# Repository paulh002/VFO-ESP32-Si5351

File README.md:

# VFO-ESP32-Si5351 v3 
v3 is moved to other repository ESPVfo32 the version in this repo is based on older libraries of lvgl 7 and not maintained by me any more.

# VFO-ESP32-Si5351 v2.43 beta
In this version the GUI is changed to support touch using simple buttons at the bottom of the screen.
It took some time to have them also supported by using the rotary encoder.

Changes:
- TFT library has been changed to TFT_eSPI, download the library in Arduine IDE and config the User_Setup.h to your configuration or use the one in this repository for the PCB in this project
- LGVL library is used for GUI. Install in Arduino IDE LVGL library (not Arduino LVGL) copy the lv_conf.h to you library directory to config lvgl library or create your own config file to your liking.
- I use now Visual Studio Community 2019 with Visual Micro to compile the project. But Arduino IDE is also supported.
- source has been moved to vfo_esp32_si5351 directory
- vfo1 and vfo2 support
- gui supported wifi configuration
- gui supported si5351 configuration
- libraries are moved to library directory 
- source code includes a visual studio project file
- TX GUI with power and SWR measurement
- GUI supported AD8307 calibration
- Bfo adjustment, A button select bfo adjustment and use the optical encoder to change frequency.

Notes
- The si5351 library is customized for esp32 support and can be found in the library directory
- Libraries used
   -  Acebutton https://github.com/bxparks/AceButton
   -  ESP32Encoder https://github.com/madhephaestus/ESP32Encoder
   -  lvgl https://lvgl.io/

New GUI with buttons at the bottom   

# VFO-ESP32-Si5351 v2.41 beta
update-- added Power and SWR gauges

# VFO-ESP32-Si5351 v2.4 beta
Version 2.33 source code is moved to the main branch, as I am now working on a new version of the GUI based on LVGL userinterface.
This because the old userinterface became to complex to maintain if I want to add wifi management and other setup pages.
The software is not yet complete, however enough to test.

Gui supported Wifi settings

Gui supported si5351 calibration

# VFO-ESP32-Si5351 v2.33 (main branch)
Updated network functions. Added telnet support for debugging, CAT interface on port 1003 support.
CAT interface will send frequency updates when the VFO is tuned. This is used by RF-AMP and later Antenna tunner to follow the frequencies
See PWRSWR repository for the rf-amp esp32 controler with swr meter functionality. I use same VFO PCB also for rf-amp controler. 

# VFO-ESP32-Si5351 v2.32
Updated the ota software to support Arduino IDE interface, recently I have dropped the Arduino IDE for Visual Studio 2019 which gives a bit more software development support
The main changes for this version is a Network CAT support the idea is from TRXNET (TRX-Manager) unfortunally TRX-Manager is discontinued. But the idea of a CAT interface on tcp/ip is nice. I use this interface to let the VFO to communicate with other ESP32 controlers to automatic send commands to my rf-amp. Also I want to use it to communicate with my automatic antenna tuner. Will be added to github later.

# VFO-ESP32-Si5351 v2.31
Some PCB updates, added output capacitors and changed the resistor pi network on the output to simple voltage divider.
The pi network caused a higher current in the buffer transistor which causes the board to radiate some BFO frequency.
This was picked up by my IF and caused the AGC to react. It seems to be better to lower the current in the buffer transistor.
The output voltage can be regulated by adjusting the resitor divider.

# VFO-ESP32-Si5351 v2.3
I added a new version of the pcb to support Wifi and uses a buck converter for powersupply.
I am still testing if the buck converter does not generate to much noise.
Source code is adjusted to use new GPIO ports so ADC1 is only used

# VFO-ESP32-Si5351 v2.2
Now my transceiver is in a box, it is more easy to update software using wifi. This release support this. The only problem is that some analog ports will not support both ADC and wifi, in the next release I will update the PCB and rearange the analog inputs to user ADC1 only.

# VFO-ESP32-Si5351 v2.1
The PCB has a connector for analog I/O this is intended to support facilities like SWR meter, Voltage and current meter. In the src directory I have put a version of the software that support SWR measurement and CAT interface. Also some simple calibration menu's are added. But this is still in development. The code for SWR comes from Loftur E. Jónasson - TF3LJ / VE2LJX but was intended for Teensy. I made a ESP32 implementation of it and with support for ILI9341 adafruit library. 
I will update (hope fully) this extension the comming months to have full calibration capability for both si5351 and the AD8307 log detectors. A pcb for the SWR meter is also developed this I will put in a seperate repository.

# VFO-ESP32-Si5351 v2.0
The new version v 2.0 uses 2x si5351 on the pcb with buffer transistors to minimize crosstalk. The old version had about 52 db  crosstalk suppression with the new version this is much improved. I cannot hear any injected spurs any more. But will add some measurements later.
The SI5351 library is updated to support multiple si5351's.

If you are using diode double balanced mixers than a square wave is no problem. But if you want to use a jfet balanced mixer than you need to filter the output of the vfo. For this I developed a filter PCB which is controled by the vfo.

Spectrum of two seperate si5351 with buffer. (12.5 Mhz and 8.998 Mhz)

VFO build in into QRP tranceiver with hycas IF and bandpassfilters managed by esp32
The VFO uses a optical encoder for frequency adjustment and mechanical rotary for bandswitch and option selection.

Bottom side with transmitter amplifier and low-pass filter section also managed by esp32.

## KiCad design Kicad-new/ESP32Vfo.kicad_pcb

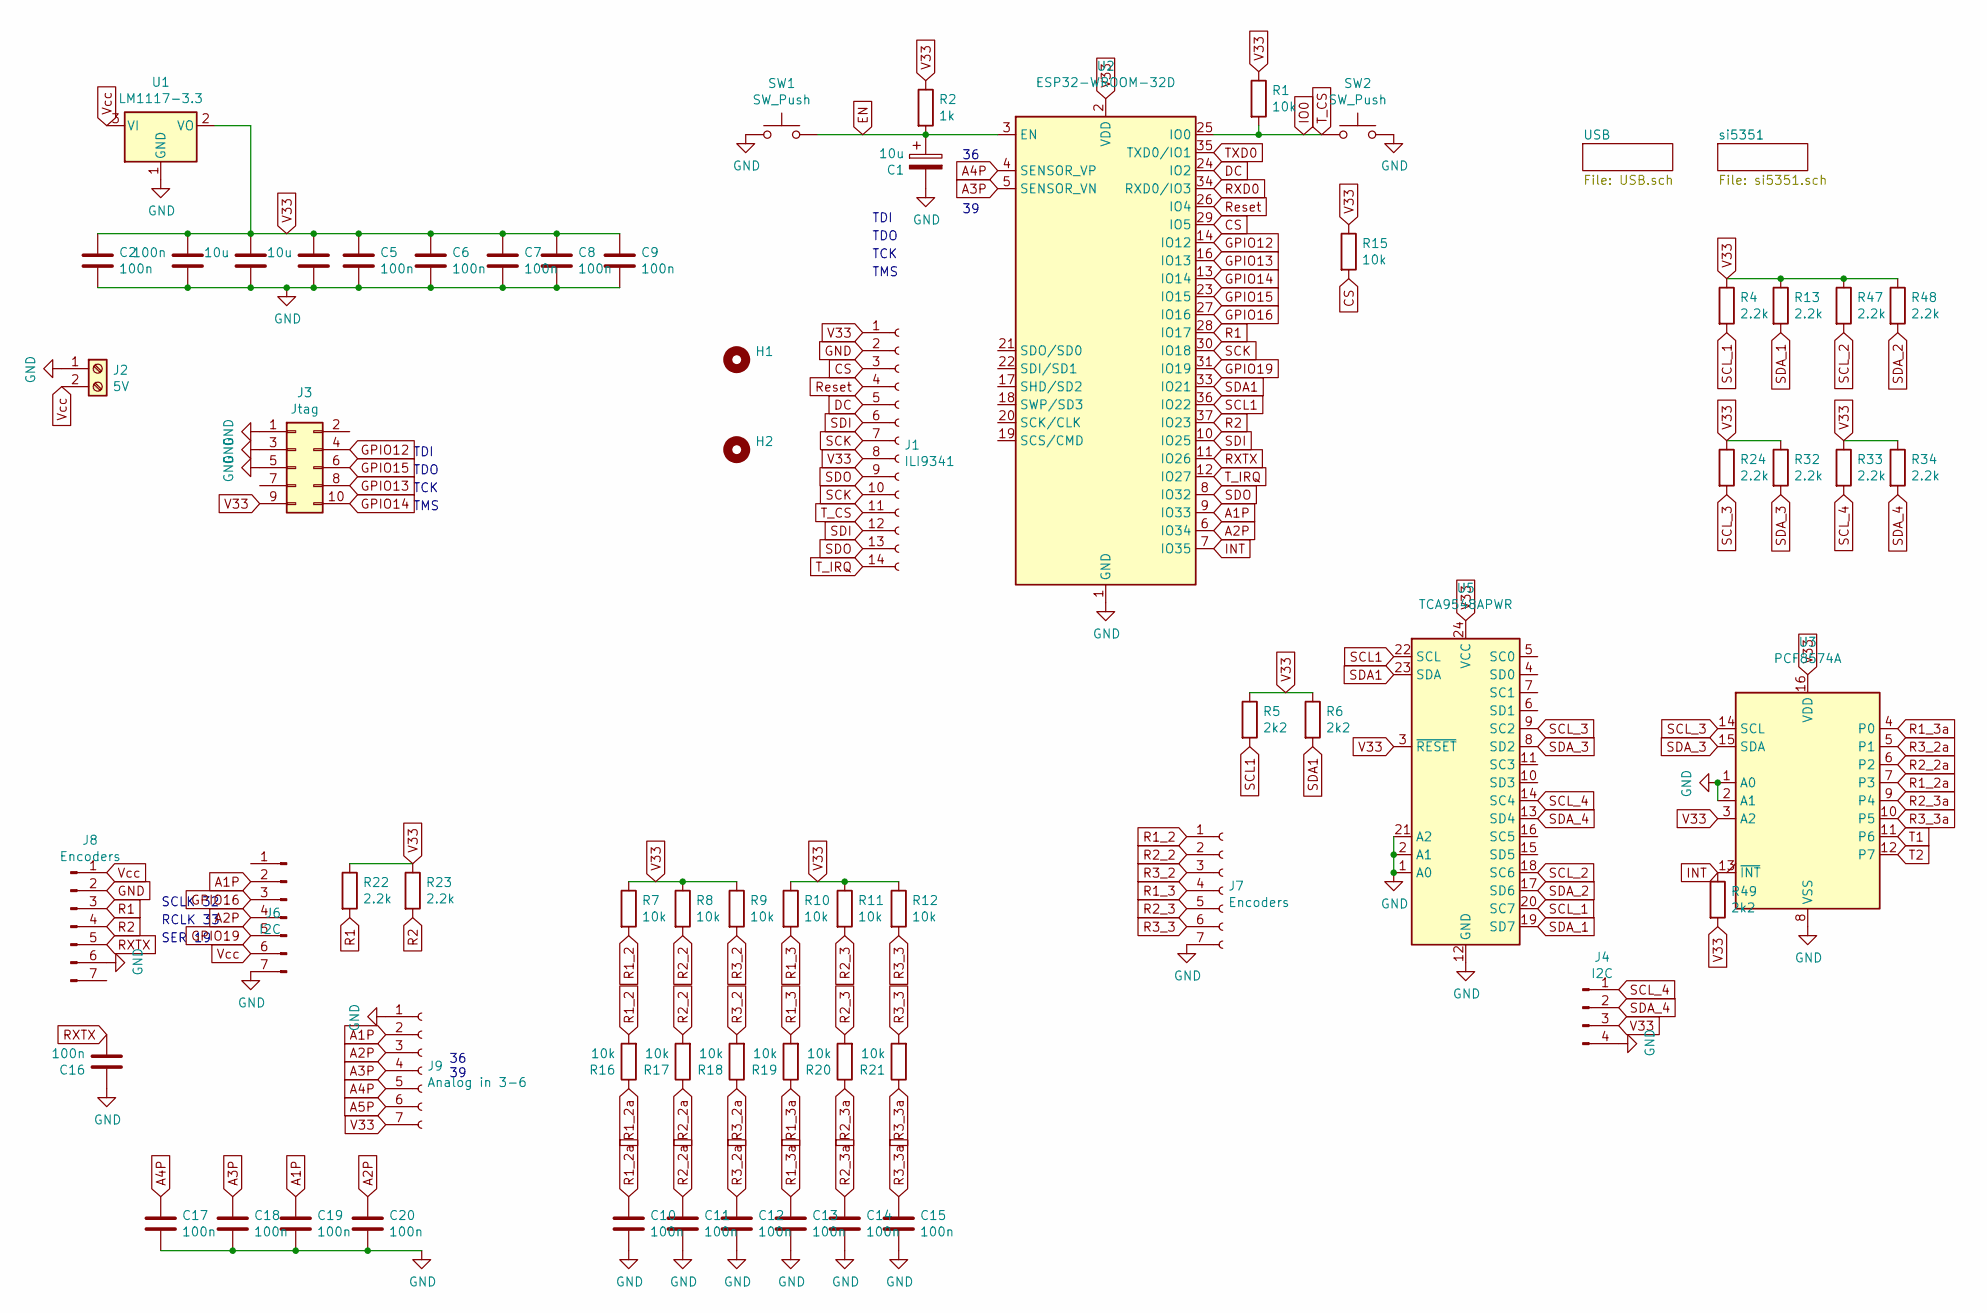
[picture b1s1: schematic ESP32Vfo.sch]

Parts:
C1, C4: 10u; C_1206_3216Metric_Pad1.42x1.75mm_HandSolder
C2, C3, C5, C6, C7, C8, C9, C10, C11, C12, C13, C14, C15, C16, C17, C18, C19, C20: 100n; C_0805_2012Metric
C34: 10u; C_0805_2012Metric
H1, H2: MountingHole_3.2mm_M3
J1: ILI9341; PinSocket_1x14_P2.54mm_Vertical
J2: 5V; TerminalBlock_MetzConnect_Type011_RT05502HBWC_1x02_P5.00mm_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
J3: Jtag; PinSocket_2x05_P2.54mm_Vertical
J4: I2C; JST_PH_S4B-PH-SM4-TB_1x04-1MP_P2.00mm_Horizontal
J6: I2C; PinSocket_1x07_P2.54mm_Vertical
J7, J8: Encoders; PinSocket_1x07_P2.54mm_Vertical
J9: Analog in 3-6; PinSocket_1x07_P2.54mm_Vertical
R1, R7, R8, R9, R10, R11, R12, R15, R16, R17, R18, R19, R20, R21: 10k; R_0805_2012Metric
R2: 1k; R_0805_2012Metric
R4, R13, R22, R23, R24, R32, R33, R34, R47, R48: 2.2k; R_0805_2012Metric
R5, R6, R49: 2k2; R_0805_2012Metric
SW1, SW2: SW_Push; TS-1088R-02526
U1: LM1117-3.3; SOT-223-3_TabPin2
U2: ESP32-WROOM-32D; ESP32-WROOM-32
U3: PCF8574A; SOP-16_7.5x10.4mm_P1.27mm
U5: TCA9548APWR; TSSOP-24_4.4x7.8mm_P0.65mm

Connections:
A1P: C19.2, J6.2, J9.2, U2.9 (IO33)
A2P: C20.2, J6.4, J9.3, U2.6 (IO34)
A3P: C18.2, J9.4, U2.5 (SENSOR_VN)
A4P: C17.2, J9.5, U2.4 (SENSOR_VP)
A5P: J9.6
CS: J1.3, R15.2, U2.29 (IO5)
DC: J1.5, U2.24 (IO2)
EN: C1.1, R2.2, SW1.2, U2.3 (EN); also elsewhere on the board
GND: C1.2, C2.1, C3.2, C4.2, C5.1, C6.1, C7.1, C8.1, C9.1, C10.1, C11.1, C12.1, C13.1, C14.1, C15.1, C16.2, C17.1, C18.1, C19.1, C20.1, C34.2, J1.2, J2.1, J3.1, J3.3, J3.5, J4.4, J6.7, J7.7, J8.2, J8.6, J9.1, SW1.1, SW2.2, U1.1 (GND), U2.1 (GND), U2.15 (GND), U2.38 (GND), U2.39 (GND), U3.1 (A0), U3.2 (A1), U3.8 (VSS), U5.1 (A0), U5.2 (A1), U5.12 (GND), U5.21 (A2); also elsewhere on the board
GPIO12: J3.4, U2.14 (IO12)
GPIO13: J3.8, U2.16 (IO13)
GPIO14: J3.10, U2.13 (IO14)
GPIO15: J3.6, U2.23 (IO15)
GPIO16: J6.3, U2.27 (IO16)
GPIO19: J6.5, U2.31 (IO19)
INT: R49.1, U2.7 (IO35), U3.13 (~INT~)
IO0: J1.11, R1.2, SW2.1, U2.25 (IO0); also elsewhere on the board
R1: J8.3, R22.2, U2.28 (IO17)
R1_2: J7.1, R7.2, R16.2
R1_2a: C10.2, R16.1, U3.7 (P3)
R1_3: J7.4, R10.2, R19.2
R1_3a: C13.2, R19.1, U3.4 (P0)
R2: J8.4, R23.2, U2.37 (IO23)
R2_3: J7.5, R11.2, R20.2
R2_3a: C14.2, R20.1, U3.9 (P4)
R3_2: J7.3, R9.2, R18.2
R3_2a: C12.2, R18.1, U3.5 (P1)
R3_3: J7.6, R12.2, R21.2
R3_3a: C15.2, R21.1, U3.10 (P5)
RXD0: U2.34 (RXD0/IO3); also elsewhere on the board
Reset: J1.4, U2.26 (IO4)
SCK: J1.7, J1.10, U2.30 (IO18)
SCL1: R5.2, U2.36 (IO22), U5.22 (SCL)
SCL_1: R4.2, U5.20 (SC7); also elsewhere on the board
SCL_2: R47.2, U5.18 (SC6); also elsewhere on the board
SCL_3: R24.2, U3.14 (SCL), U5.9 (SC2)
SCL_4: J4.1, R33.2, U5.14 (SC4)
SDA1: R6.2, U2.33 (IO21), U5.23 (SDA)
SDA_1: R13.2, U5.19 (SD7); also elsewhere on the board
SDA_2: R48.2, U5.17 (SD6); also elsewhere on the board
SDA_3: R32.2, U3.15 (SDA), U5.8 (SD2)
SDA_4: J4.2, R34.2, U5.13 (SD4)
SDI: J1.6, J1.12, U2.10 (IO25)
SDO: J1.9, J1.13, U2.8 (IO32)
T1: U3.11 (P6); also elsewhere on the board
T2: U3.12 (P7); also elsewhere on the board
TXD0: U2.35 (TXD0/IO1); also elsewhere on the board
T_IRQ: J1.14, U2.12 (IO27)
Vcc: J2.2, J6.6, J8.1, U1.3 (VI); also elsewhere on the board

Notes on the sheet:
TMS
TCK
TDO
TDI
36 39
SER 19
SCLK 32
RCLK 33

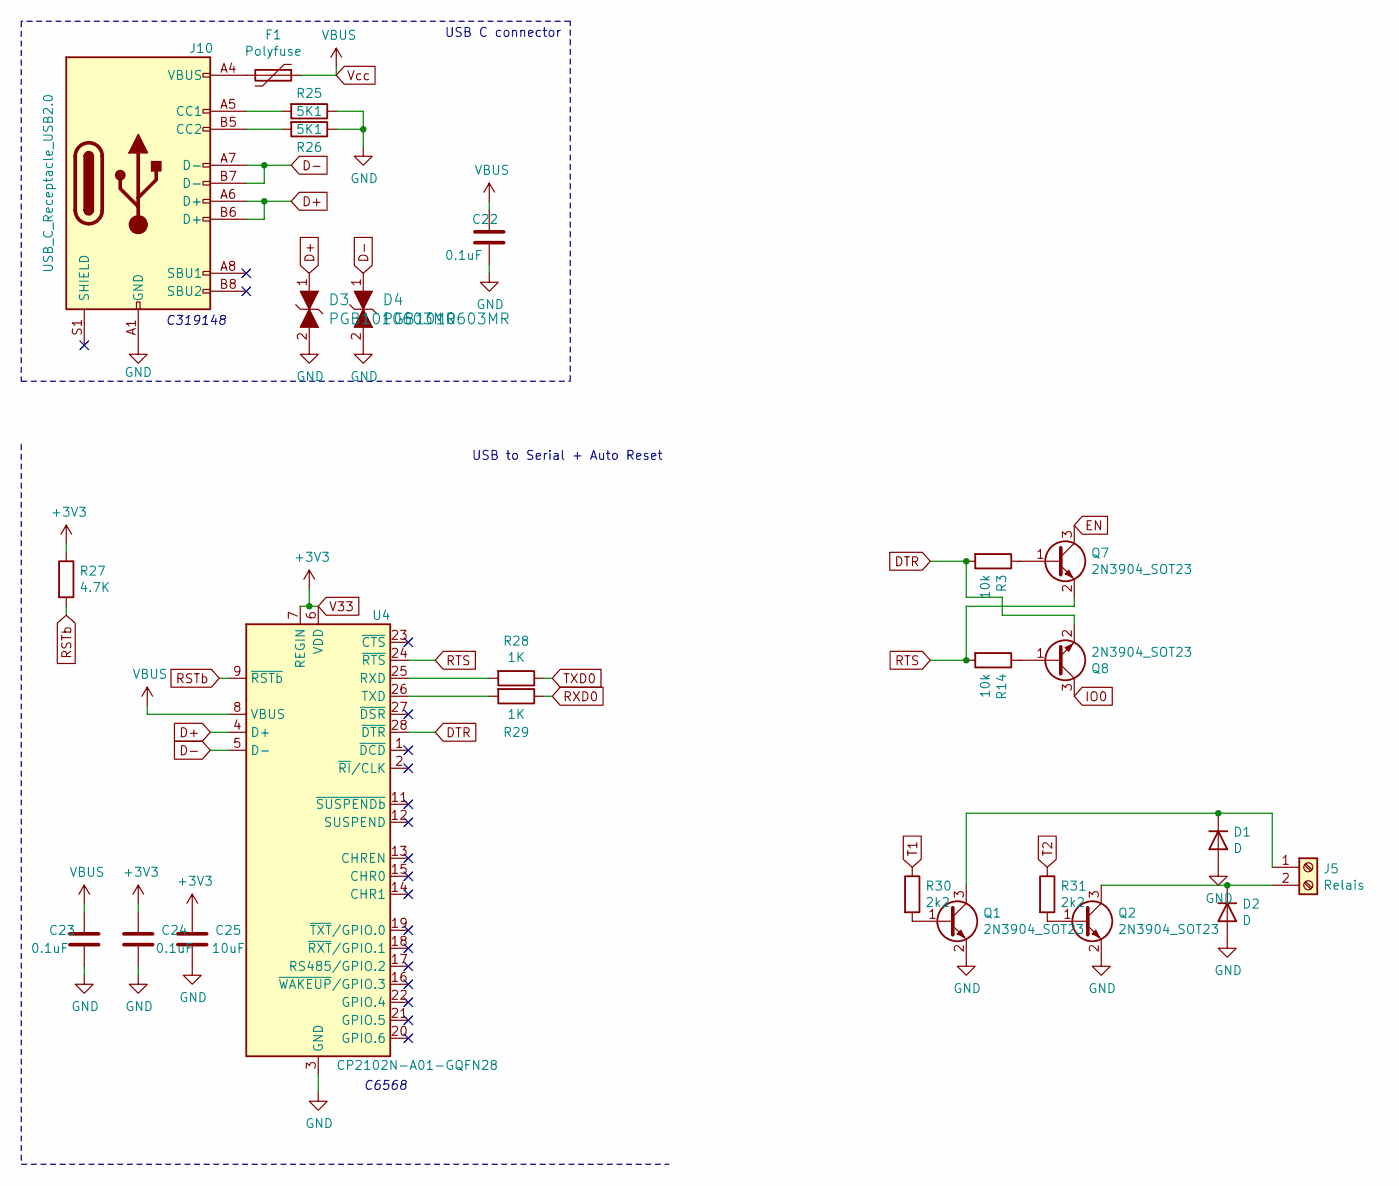
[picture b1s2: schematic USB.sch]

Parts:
C22, C23, C24: 0.1uF; C_0805_2012Metric
C25: 10uF; C_0805_2012Metric
D1, D2: D; D_SOD-323
D3, D4: PGB1010603MR; 0603; MPN PGB1010603MR; Digi-Key_PN F2594CT-ND
F1: Polyfuse; Fuse_0805_2012Metric
J5: Relais; PinHeader_1x02_P2.54mm_Vertical
J10: USB_C_Receptacle_USB2.0; USB_C_Receptacle_XKB_U262-16XN-4BVC11
Q1, Q2, Q7, Q8: 2N3904_SOT23; SOT-23
R3, R14: 10k; R_0805_2012Metric
R25, R26: 5K1; R_0805_2012Metric
R27: 4.7K; R_0805_2012Metric
R28, R29: 1K; R_0805_2012Metric
R30, R31: 2k2; R_0805_2012Metric
U4: CP2102N-A01-GQFN28; QFN-28-1EP_5x5mm_P0.5mm_EP3.35x3.35mm

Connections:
D+: D3.1, J10.A6 (D+), J10.B6 (D+), U4.4 (D+)
D-: D4.1, J10.A7 (D-), J10.B7 (D-), U4.5 (D-)
DTR: Q8.2 (E), R3.2, U4.28 (~DTR)
EN: Q7.3 (C); also elsewhere on the board
GND: C22.2, C23.2, C24.2, C25.2, D1.2 (A), D2.2 (A), D3.2, D4.2, J10.A1 (GND), J10.A12 (GND), J10.B1 (GND), J10.B12 (GND), Q1.2 (E), Q2.2 (E), R25.1, R26.1, U4.3 (GND), U4.29 (GND); also elsewhere on the board
IO0: Q8.3 (C); also elsewhere on the board
unnamed: D1.1 (K), J5.1, Q1.3 (C)
unnamed: D2.1 (K), J5.2, Q2.3 (C)
unnamed: F1.2, J10.A4 (VBUS), J10.A9 (VBUS), J10.B4 (VBUS), J10.B9 (VBUS)
unnamed: J10.A5 (CC1), R25.2
unnamed: J10.B5 (CC2), R26.2
unnamed: Q1.1 (B), R30.2
unnamed: Q2.1 (B), R31.2
unnamed: Q7.1 (B), R3.1
unnamed: Q8.1 (B), R14.1
unnamed: R28.2, U4.25 (RXD)
unnamed: R29.2, U4.26 (TXD)
RSTb: R27.2, U4.9 (~RSTb)
RTS: Q7.2 (E), R14.2, U4.24 (~RTS)
RXD0: R29.1; also elsewhere on the board
T1: R30.1; also elsewhere on the board
T2: R31.1; also elsewhere on the board
TXD0: R28.1; also elsewhere on the board
Vcc: C22.1, C23.1, F1.1, U4.8 (VBUS); also elsewhere on the board

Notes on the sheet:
C6568
USB to Serial + Auto Reset
USB C connector
C319148

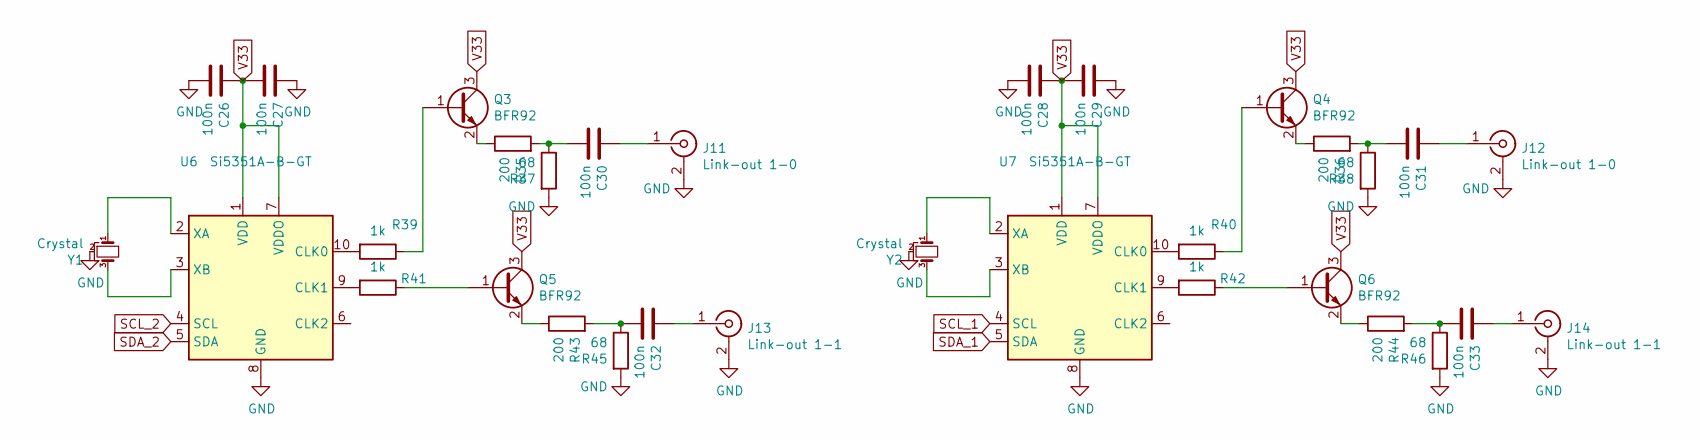
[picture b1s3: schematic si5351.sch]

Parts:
C26, C27, C28, C29, C30, C31, C32, C33: 100n; C_0805_2012Metric
J11, J12: Link-out 1-0; SMA_Amphenol_132134_Vertical
J13, J14: Link-out 1-1; SMA_Amphenol_132134_Vertical
Q3, Q4, Q5, Q6: BFR92; SOT-23
R35, R36, R43, R44: 200; R_0805_2012Metric
R37, R38, R45, R46: 68; R_0805_2012Metric
R39, R40, R41, R42: 1k; R_0805_2012Metric
U6, U7: Si5351A-B-GT; MSOP-10_3x3mm_P0.5mm
Y1, Y2: Crystal; Crystal_SMD_TXC_7M-4Pin_3.2x2.5mm_HandSoldering

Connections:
GND: C26.1, C27.2, C28.1, C29.2, J11.2 (Ext), J12.2 (Ext), J13.2 (Ext), J14.2 (Ext), R37.2, R38.2, R45.2, R46.2, U6.8 (GND), U7.8 (GND), Y1.2, Y2.2; also elsewhere on the board
unnamed: C30.1, R35.2, R37.1
unnamed: C30.2, J11.1 (In)
unnamed: C31.1, R36.2, R38.1
unnamed: C31.2, J12.1 (In)
unnamed: C32.1, R43.2, R45.1
unnamed: C32.2, J13.1 (In)
unnamed: C33.1, R44.2, R46.1
unnamed: C33.2, J14.1 (In)
unnamed: Q3.1 (B), R39.1
unnamed: Q3.2 (E), R35.1
unnamed: Q4.1 (B), R40.1
unnamed: Q4.2 (E), R36.1
unnamed: Q5.1 (B), R41.1
unnamed: Q5.2 (E), R43.1
unnamed: Q6.1 (B), R42.1
unnamed: Q6.2 (E), R44.1
unnamed: R39.2, U6.10 (CLK0)
unnamed: R40.2, U7.10 (CLK0)
unnamed: R41.2, U6.9 (CLK1)
unnamed: R42.2, U7.9 (CLK1)
unnamed: U6.2 (XA), Y1.1
unnamed: U6.3 (XB), Y1.3
unnamed: U7.2 (XA), Y2.1
unnamed: U7.3 (XB), Y2.3
SCL_1: U7.4 (SCL); also elsewhere on the board
SCL_2: U6.4 (SCL); also elsewhere on the board
SDA_1: U7.5 (SDA); also elsewhere on the board
SDA_2: U6.5 (SDA); also elsewhere on the board

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
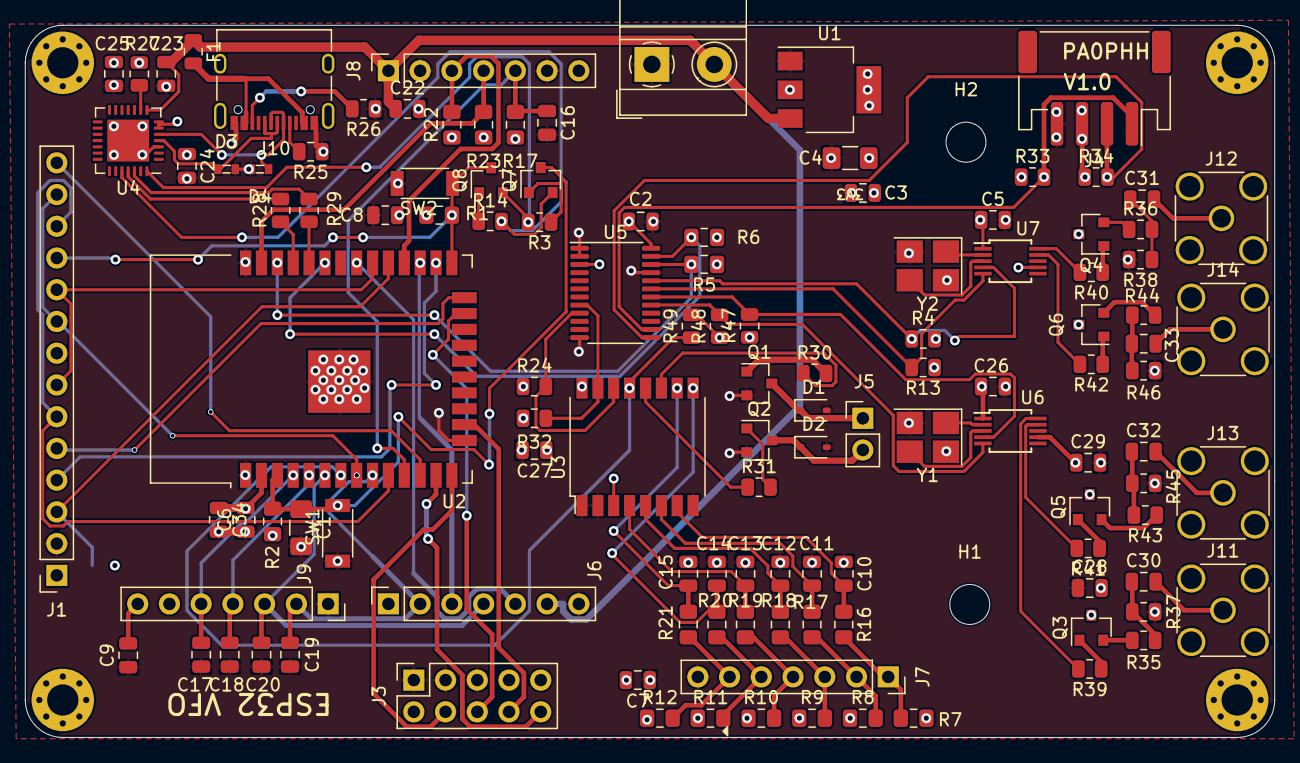
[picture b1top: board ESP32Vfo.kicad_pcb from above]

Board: 4 copper layers, 100.0 x 57.0 mm, 127 parts (1 on the bottom side), 92 nets.

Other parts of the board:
H1#2, H2#2, H3, H4: MountingHole; MountingHole_2.5mm_Pad_Via
R17#2: 10k; R_0805_2012Metric_Pad1.15x1.40mm_HandSolder

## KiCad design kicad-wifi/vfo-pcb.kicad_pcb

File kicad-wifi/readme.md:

Kicad files new version with wifi.
This version uses a buck converter for powersupply, the lm7805 is not able to supply a stable enough 5v for wifi use
I am still testing if the buck converter does not generate to much noise

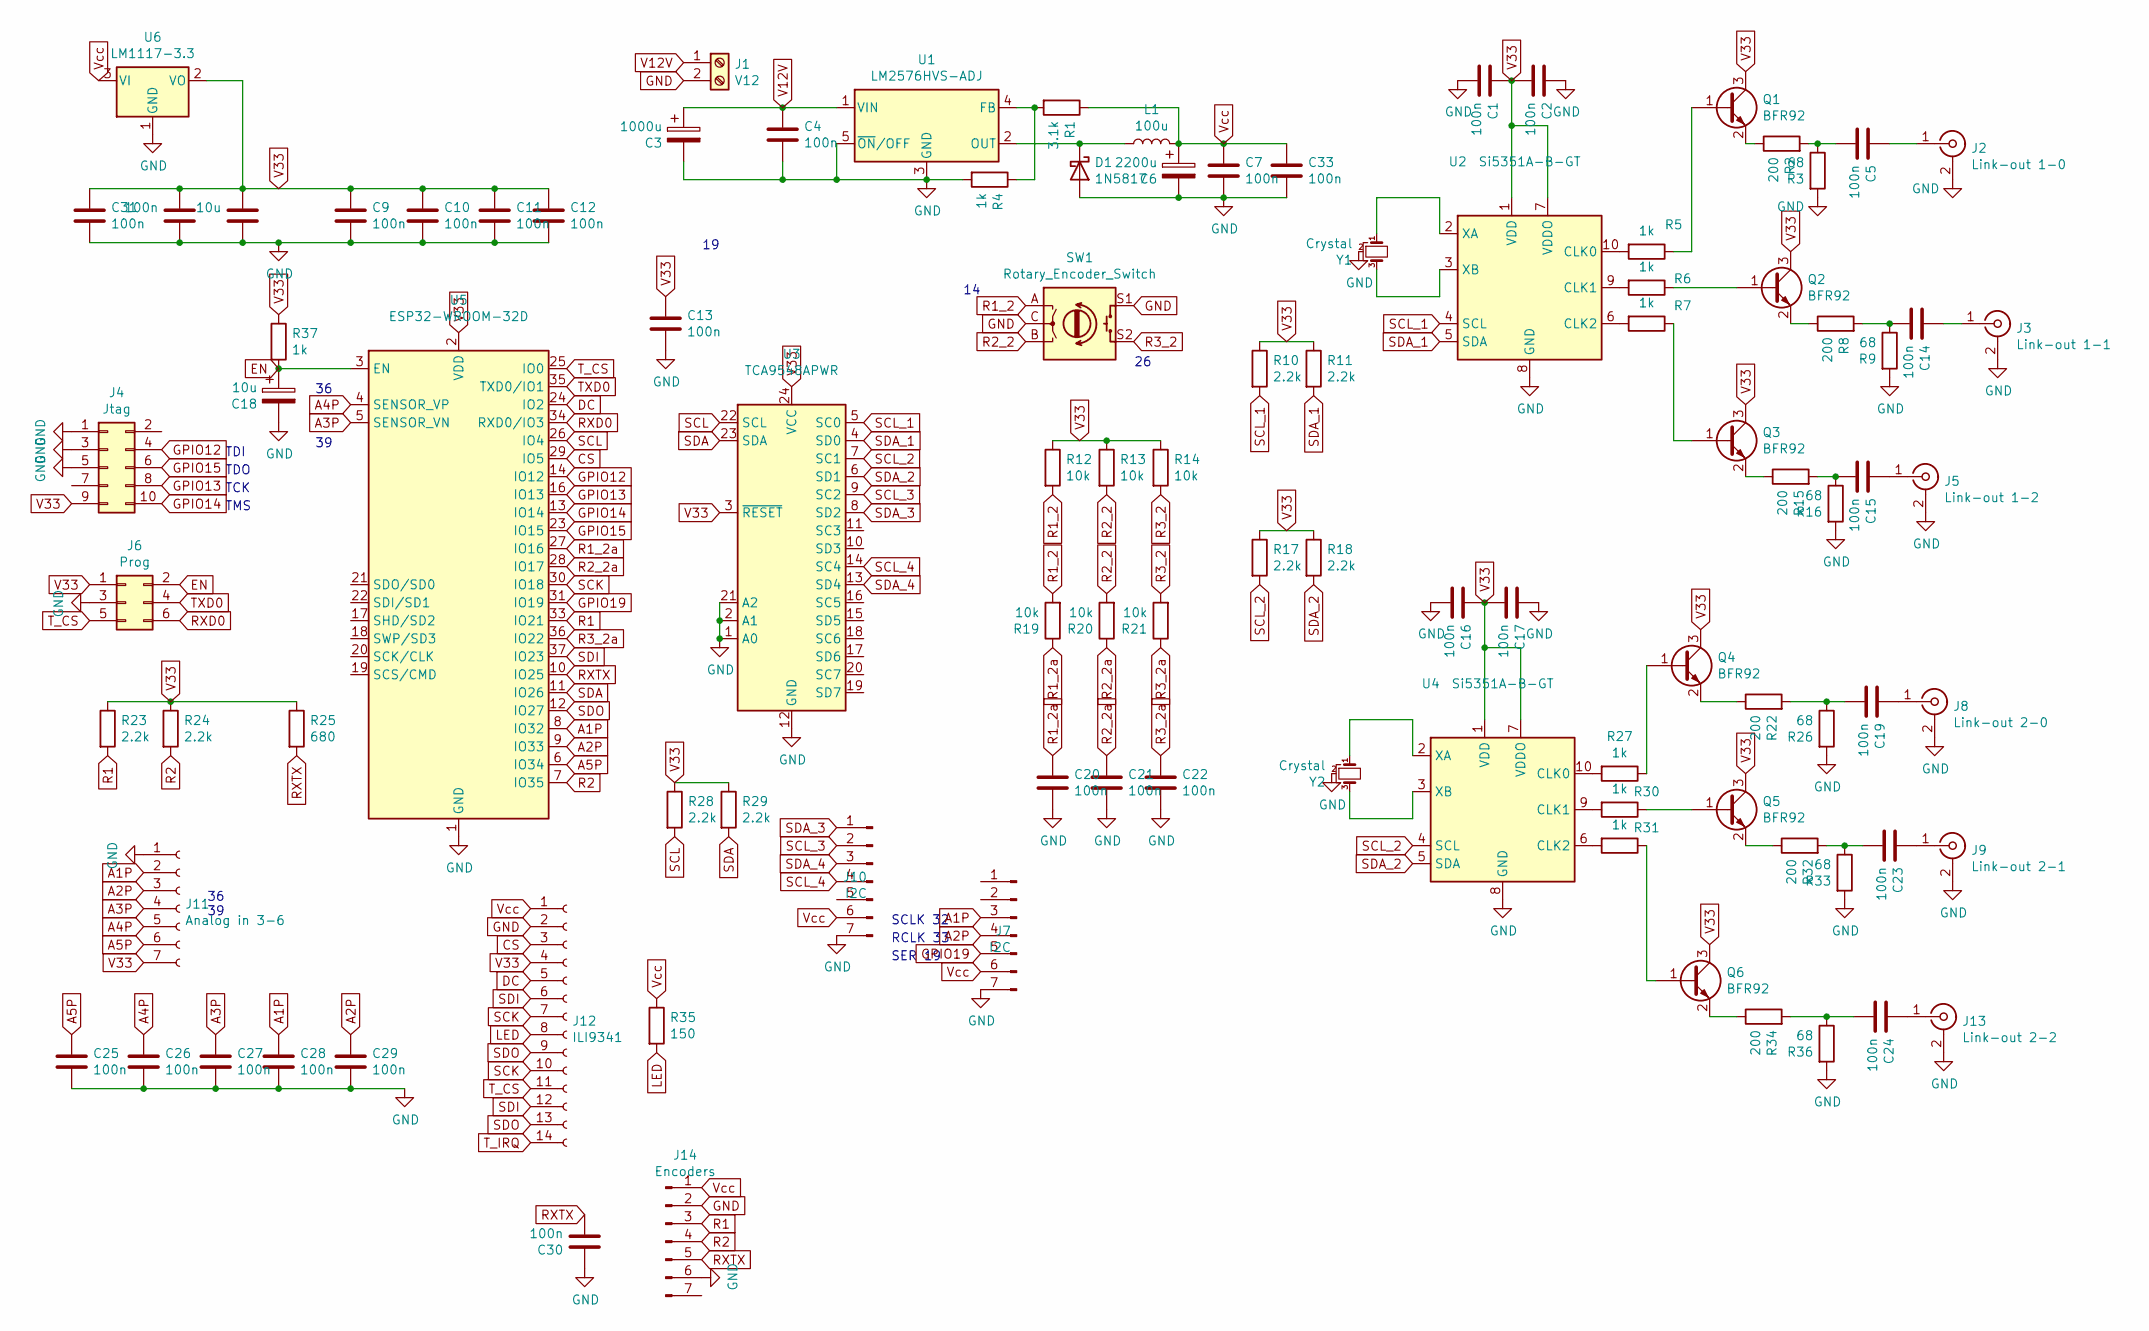
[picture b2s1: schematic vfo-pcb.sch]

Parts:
C1, C2, C4, C5, C7, C8, C9, C10, C11, C12, C13, C14, C15, C16, C17, C19, C20, C21, C22, C23, C24, C25, C26, C27, C28, C29, C30, C31, C33: 100n; C_1206_3216Metric_Pad1.42x1.75mm_HandSolder
C3: 1000u; CP_Radial_D10.0mm_P5.00mm
C6: 2200u; CP_Radial_D10.0mm_P5.00mm
C18, C32: 10u; C_1206_3216Metric_Pad1.42x1.75mm_HandSolder
D1: 1N5817; D_DO-41_SOD81_P10.16mm_Horizontal
J1: V12; TerminalBlock_MetzConnect_Type011_RT05502HBWC_1x02_P5.00mm_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
J2: Link-out 1-0; SMA_Amphenol_132134_Vertical
J3: Link-out 1-1; SMA_Amphenol_132134_Vertical
J4: Jtag; PinSocket_2x05_P2.54mm_Vertical
J5: Link-out 1-2; SMA_Amphenol_132134_Vertical
J6: Prog; PinSocket_2x03_P2.54mm_Vertical
J7, J10: I2C; PinSocket_1x07_P2.54mm_Vertical
J8: Link-out 2-0; SMA_Amphenol_132134_Vertical
J9: Link-out 2-1; SMA_Amphenol_132134_Vertical
J11: Analog in 3-6; PinSocket_1x07_P2.54mm_Vertical
J12: ILI9341; PinSocket_1x14_P2.54mm_Vertical
J13: Link-out 2-2; SMA_Amphenol_132134_Vertical
J14: Encoders; PinSocket_1x07_P2.54mm_Vertical
L1: 100u; L_Bourns-SRU1028_10.0x10.0mm
Q1, Q2, Q3, Q4, Q5, Q6: BFR92; SOT-23
R1: 3.1k; R_1206_3216Metric_Pad1.42x1.75mm_HandSolder
R2, R8, R15, R22, R32, R34: 200; R_1206_3216Metric_Pad1.42x1.75mm_HandSolder
R3, R9, R16, R26, R33, R36: 68; R_1206_3216Metric_Pad1.42x1.75mm_HandSolder
R4, R5, R6, R7, R27, R30, R31, R37: 1k; R_1206_3216Metric_Pad1.42x1.75mm_HandSolder
R10, R11, R17, R18, R23, R24, R28, R29: 2.2k; R_1206_3216Metric_Pad1.42x1.75mm_HandSolder
R12, R13, R14, R19, R20, R21: 10k; R_1206_3216Metric_Pad1.42x1.75mm_HandSolder
R25: 680; R_1206_3216Metric_Pad1.42x1.75mm_HandSolder
R35: 150; R_1206_3216Metric_Pad1.42x1.75mm_HandSolder
SW1: Rotary_Encoder_Switch; RotaryEncoder_Alps_EC11E-Switch_Vertical_H20mm
U1: LM2576HVS-ADJ; TO-220-5_Horizontal_TabDown
U2, U4: Si5351A-B-GT; MSOP-10_3x3mm_P0.5mm
U3: TCA9548APWR; TSSOP-24_4.4x7.8mm_P0.65mm
U5: ESP32-WROOM-32D; ESP32-WROOM-32
U6: LM1117-3.3; SOT-223-3_TabPin2
Y1, Y2: Crystal; Crystal_SMD_TXC_7M-4Pin_3.2x2.5mm_HandSoldering

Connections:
A1P: C28.2, J7.3, J11.2, U5.8 (IO32)
A2P: C29.2, J7.4, J11.3, U5.9 (IO33)
A3P: C27.2, J11.4, U5.5 (SENSOR_VN)
A4P: C26.2, J11.5, U5.4 (SENSOR_VP)
A5P: C25.2, J11.6, U5.6 (IO34)
CS: J12.3, U5.29 (IO5)
DC: J12.5, U5.24 (IO2)
EN: C18.1, J6.2, R37.2, U5.3 (EN)
GND: C1.1, C2.2, C3.2, C4.1, C6.2, C7.1, C8.2, C9.1, C10.1, C11.1, C12.1, C13.1, C16.1, C17.2, C18.2, C20.1, C21.1, C22.1, C25.1, C26.1, C27.1, C28.1, C29.1, C30.2, C31.1, C32.2, C33.1, D1.2 (A), J1.2, J2.2 (Ext), J3.2 (Ext), J4.1, J4.3, J4.5, J5.2 (Ext), J6.3, J7.7, J8.2 (Ext), J9.2 (Ext), J10.7, J11.1, J12.2, J13.2 (Ext), J14.2, J14.6, R3.2, R4.2, R9.2, R16.2, R26.2, R33.2, R36.2, SW1.C, SW1.S1, U1.3 (GND), U1.5 (~ON~/OFF), U2.8 (GND), U3.1 (A0), U3.2 (A1), U3.12 (GND), U3.21 (A2), U4.8 (GND), U5.1 (GND), U5.15 (GND), U5.38 (GND), U5.39 (GND), U6.1 (GND), Y1.2, Y2.2
GPIO12: J4.4, U5.14 (IO12)
GPIO13: J4.8, U5.16 (IO13)
GPIO14: J4.10, U5.13 (IO14)
GPIO15: J4.6, U5.23 (IO15)
GPIO19: J7.5, U5.31 (IO19)
LED: J12.8, R35.2
unnamed: C5.1, R2.2, R3.1
unnamed: C5.2, J2.1 (In)
unnamed: C14.1, R8.2, R9.1
unnamed: C14.2, J3.1 (In)
unnamed: C15.1, R15.2, R16.1
unnamed: C15.2, J5.1 (In)
unnamed: C19.1, R22.2, R26.1
unnamed: C19.2, J8.1 (In)
unnamed: C23.1, R32.2, R33.1
unnamed: C23.2, J9.1 (In)
unnamed: C24.1, R34.2, R36.1
unnamed: C24.2, J13.1 (In)
unnamed: D1.1 (K), L1.1, U1.2 (OUT)
unnamed: Q1.1 (B), R5.1
unnamed: Q1.2 (E), R2.1
unnamed: Q2.1 (B), R6.1
unnamed: Q2.2 (E), R8.1
unnamed: Q3.1 (B), R7.1
unnamed: Q3.2 (E), R15.1
unnamed: Q4.1 (B), R27.1
unnamed: Q4.2 (E), R22.1
unnamed: Q5.1 (B), R30.1
unnamed: Q5.2 (E), R32.1
unnamed: Q6.1 (B), R31.1
unnamed: Q6.2 (E), R34.1
unnamed: R1.2, R4.1, U1.4 (FB)
unnamed: R5.2, U2.10 (CLK0)
unnamed: R6.2, U2.9 (CLK1)
unnamed: R7.2, U2.6 (CLK2)
unnamed: R27.2, U4.10 (CLK0)
unnamed: R30.2, U4.9 (CLK1)
unnamed: R31.2, U4.6 (CLK2)
unnamed: U2.2 (XA), Y1.1
unnamed: U2.3 (XB), Y1.3
unnamed: U4.2 (XA), Y2.1
unnamed: U4.3 (XB), Y2.3
R1: J14.3, R23.2, U5.33 (IO21)
R1_2: R12.2, R19.2, SW1.A
R1_2a: C20.2, R19.1, U5.27 (IO16)
R2: J14.4, R24.2, U5.7 (IO35)
R2_2: R13.2, R20.2, SW1.B
R2_2a: C21.2, R20.1, U5.28 (IO17)
R3_2: R14.2, R21.2, SW1.S2
R3_2a: C22.2, R21.1, U5.36 (IO22)
RXD0: J6.6, U5.34 (RXD0/IO3)
RXTX: C30.1, J14.5, R25.2, U5.10 (IO25)
SCK: J12.7, J12.10, U5.30 (IO18)
SCL: R28.2, U3.22 (SCL), U5.26 (IO4)
SCL_1: R10.2, U2.4 (SCL), U3.5 (SC0)
SCL_2: R17.2, U3.7 (SC1), U4.4 (SCL)
SCL_3: J10.2, U3.9 (SC2)
SCL_4: J10.4, U3.14 (SC4)
SDA: R29.2, U3.23 (SDA), U5.11 (IO26)
SDA_1: R11.2, U2.5 (SDA), U3.4 (SD0)
SDA_2: R18.2, U3.6 (SD1), U4.5 (SDA)
SDA_3: J10.1, U3.8 (SD2)
SDA_4: J10.3, U3.13 (SD4)
SDI: J12.6, J12.12, U5.37 (IO23)
SDO: J12.9, J12.13, U5.12 (IO27)
TXD0: J6.4, U5.35 (TXD0/IO1)
T_CS: J6.5, J12.11, U5.25 (IO0)
T_IRQ: J12.14
V12V: C3.1, C4.2, J1.1, U1.1 (VIN)
V33: C1.2, C2.1, C8.1, C9.2, C10.2, C11.2, C12.2, C13.2, C16.2, C17.1, C31.2, C32.1, J4.9, J6.1, J11.7, J12.4, Q1.3 (C), Q2.3 (C), Q3.3 (C), Q4.3 (C), Q5.3 (C), Q6.3 (C), R10.1, R11.1, R12.1, R13.1, R14.1, R17.1, R18.1, R23.1, R24.1, R25.1, R28.1, R29.1, R37.1, U2.1 (VDD), U2.7 (VDDO), U3.3 (~RESET), U3.24 (VCC), U4.1 (VDD), U4.7 (VDDO), U5.2 (VDD), U6.2 (VO)
Vcc: C6.1, C7.2, C33.2, J7.6, J10.6, J12.1, J14.1, L1.2, R1.1, R35.1, U6.3 (VI)

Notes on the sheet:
36 39
TMS
TCK
TDO
TDI
SER 19
RCLK 33
SCLK 32

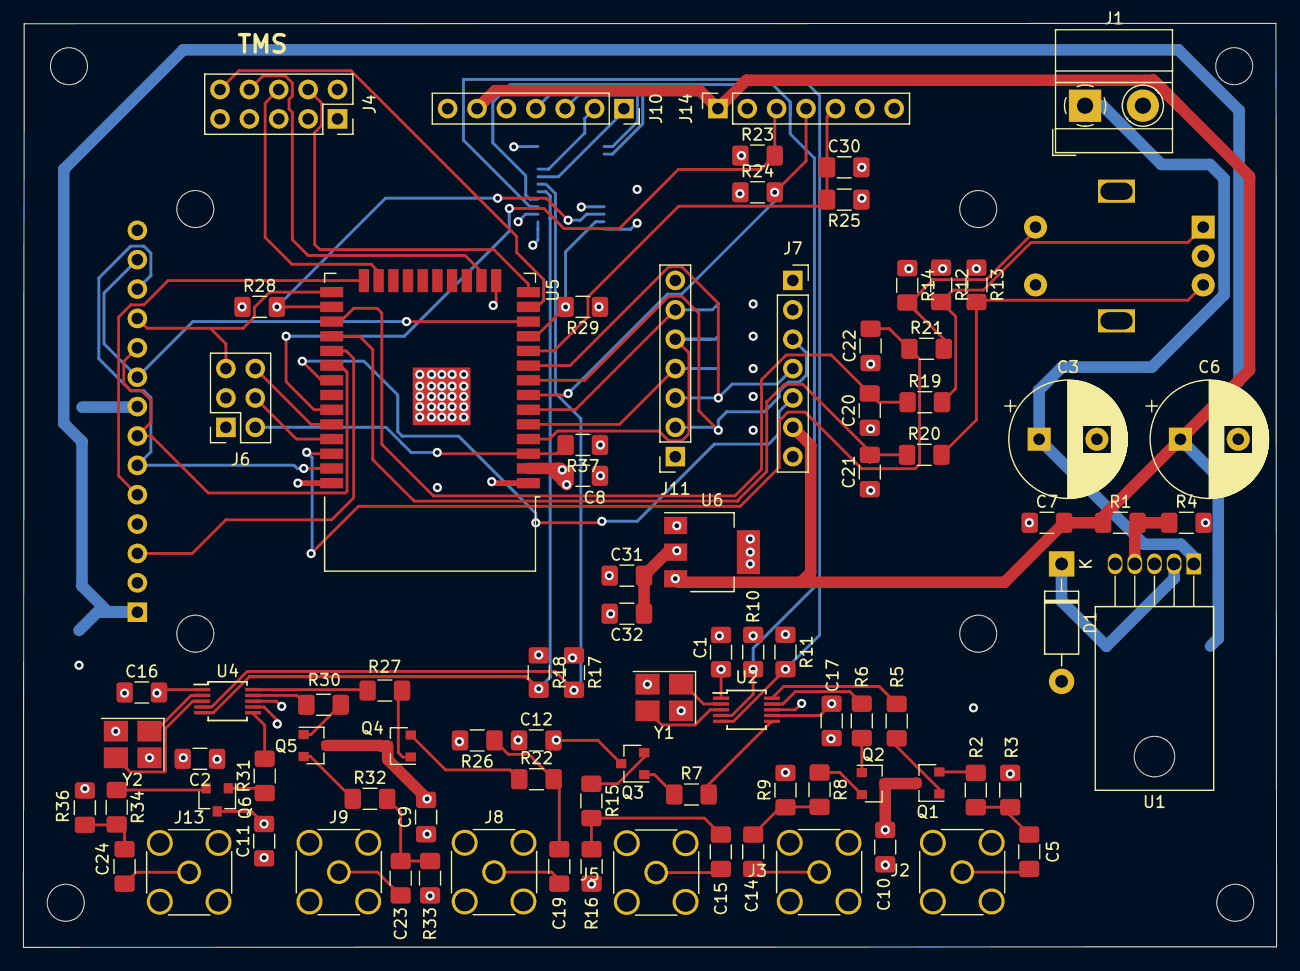
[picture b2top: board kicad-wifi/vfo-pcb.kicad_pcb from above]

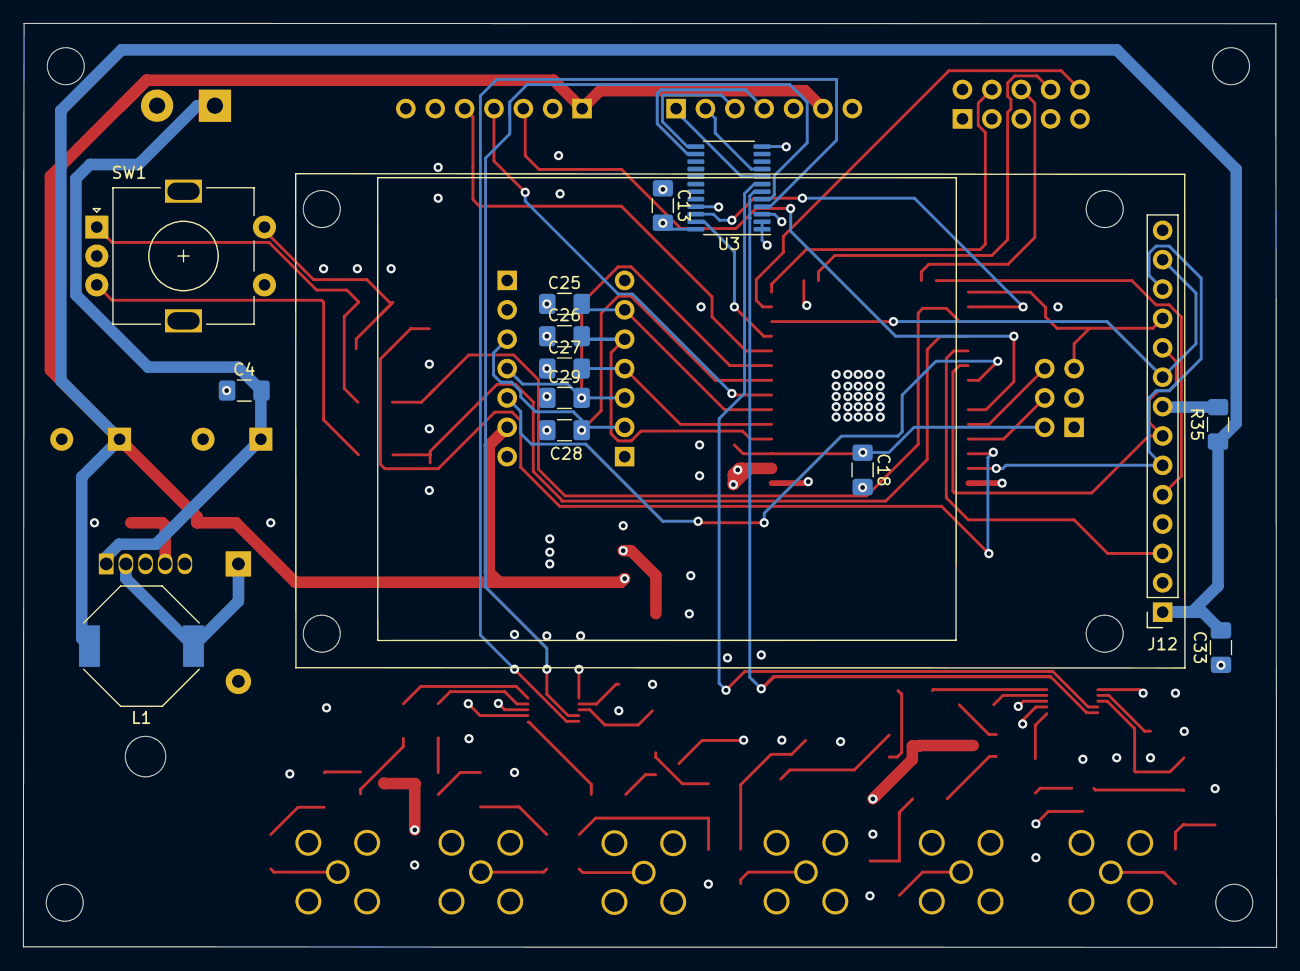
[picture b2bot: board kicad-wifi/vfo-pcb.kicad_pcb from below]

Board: 4 copper layers, 108.4 x 79.9 mm, 109 parts (14 on the bottom side), 79 nets.

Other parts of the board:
 : MountingHole_3.2mm_M3
 #2,  #3,  #4,  #5,  #6,  #7,  #8: MountingHole_3.2mm_M3
